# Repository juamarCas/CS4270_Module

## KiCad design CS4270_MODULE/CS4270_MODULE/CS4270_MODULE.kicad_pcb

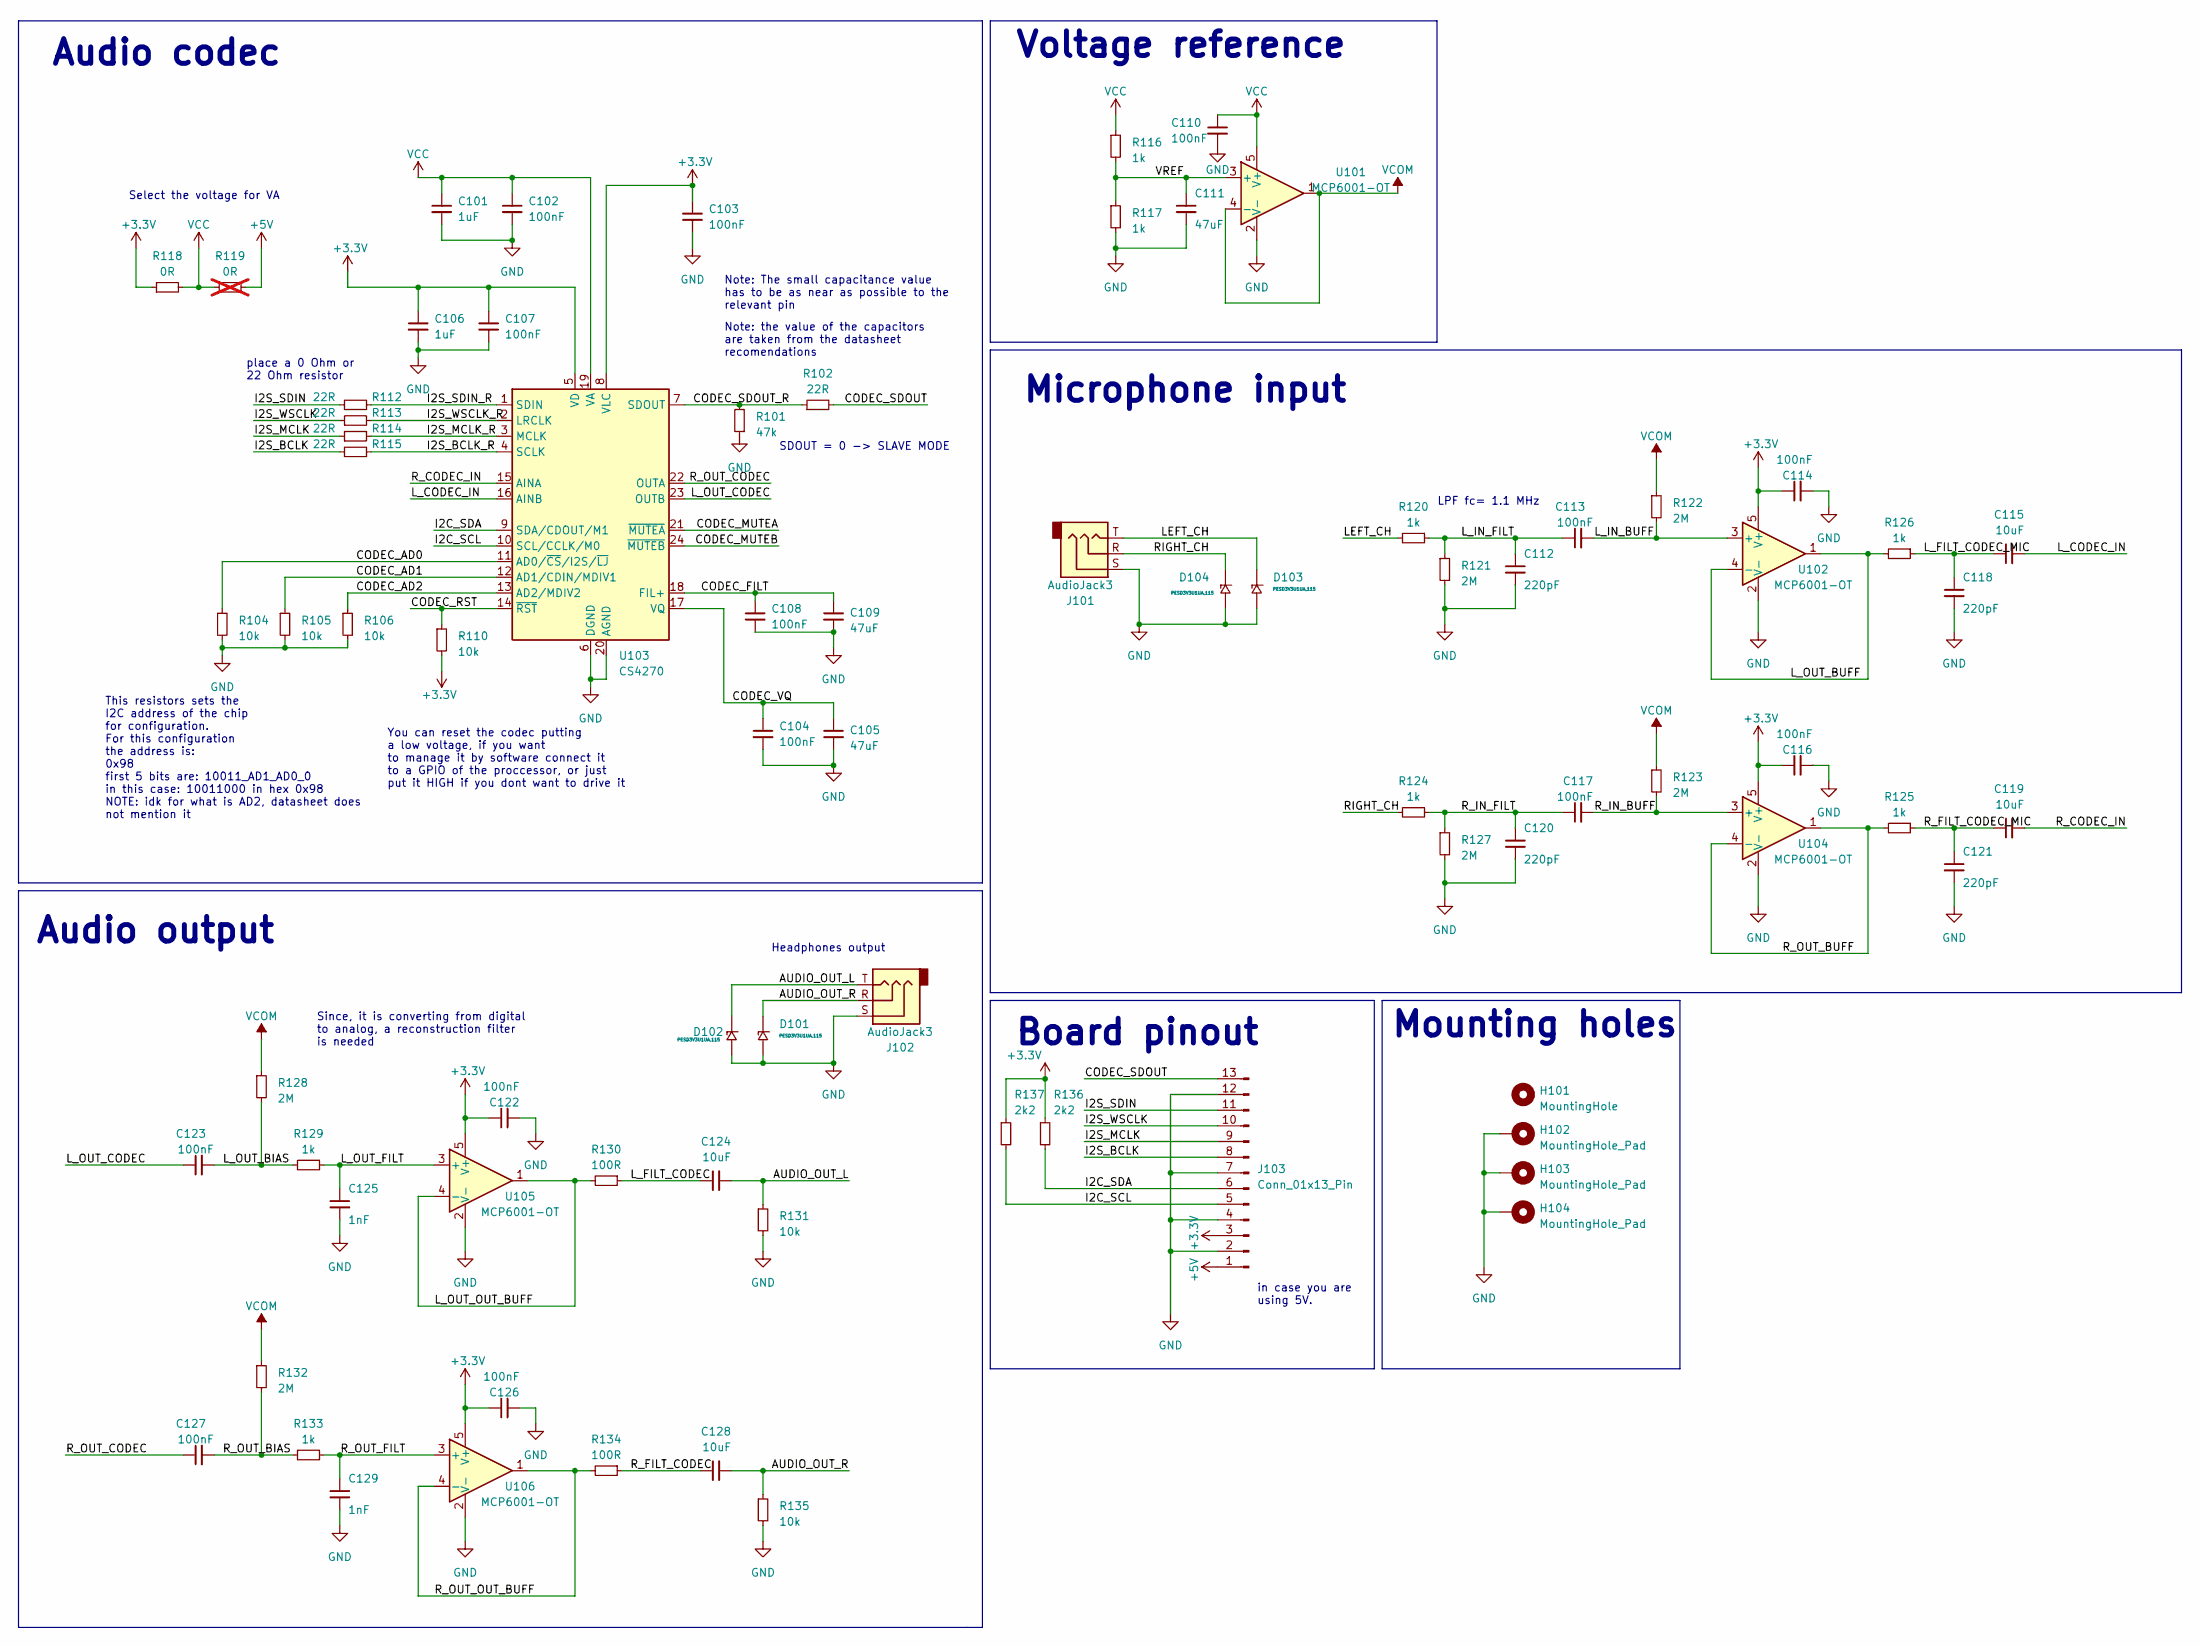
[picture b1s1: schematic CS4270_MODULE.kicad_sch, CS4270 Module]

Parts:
C101, C106: 1uF; C_0402_1005Metric; Mfr Part# GRM155R61E105MA12D
C102, C103, C104, C107, C108, C110, C113, C114, C116, C117, C122, C123, C126, C127: 100nF; C_0402_1005Metric; Mfr Part# C1005X7R1C104K050BC
C105, C109, C111: 47uF; C_0603_1608Metric; Mfr Part# 0603ZG474ZAT2A
C112, C118, C120, C121: 220pF; C_0603_1608Metric; Mfr Part# C0603C221G3HACTU
C115, C119, C124, C128: 10uF; C_0805_2012Metric; Mfr Part# GRM21BR61C106KE15K
C125, C129: 1nF; C_0402_1005Metric; Mfr Part# GRM1555C1H102JA1J
D101, D102, D103, D104: PESD3V3U1UA,115; SOD-323-2; Mfr Part# PESD3V3U1UA,115
H101: MountingHole; MountingHole_2.2mm_M2
H102: MountingHole_Pad; MountingHole_2.2mm_M2_Pad_TopBottom
H103, H104: MountingHole_Pad; MountingHole_2.2mm_M2_DIN965_Pad_TopBottom
J101, J102: AudioJack3; JAC_TRS_3.5mm_SMD; Mfr Part# 35RASMT2BHSNTRX
J103: Conn_01x13_Pin; PinHeader_1x13_P2.54mm_Vertical
R101: 47k; R_0603_1608Metric; Mfr Part# ERJ-3GEYJ473V
R102, R112, R113, R114, R115: 22R; R_0603_1608Metric; Mfr Part# ERJ-PA3F22R0V
R104, R105, R106, R110, R131, R135: 10k; R_0805_2012Metric; Mfr Part# CR0805-JW-103ELF
R116, R117, R120, R124, R125, R126, R129, R133: 1k; R_0603_1608Metric; Mfr Part# CR0603-FX-1001ELF
R118: 0R; R_0603_1608Metric; Mfr Part# ERJ-3GEY0R00V
R119: 0R; R_0603_1608Metric; Mfr Part# ERJ-3GEY0R00V; not fitted
R121, R122, R123, R127, R128, R132: 2M; R_0805_2012Metric; Mfr Part# RC0805JR-072M2L
R130, R134: 100R; R_0603_1608Metric; Mfr Part# CR0603-FX-1000ELF
R136, R137: 2k2; R_0805_2012Metric; Mfr Part# CR0805-JW-222ELF
U101, U102, U104, U105, U106: MCP6001-OT; SOT-23-5; Mfr Part# MCP6001UT-I/OT
U103: CS4270; TSSOP-24_4.4x7.8mm_P0.65mm; Mfr Part# CS4270-CZZ

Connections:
+3V3: C103.1, C106.1, C107.1, C114.1, C116.1, C122.1, C126.1, J103.3, R110.2, R118.1, R136.1, R137.1, U102.5 (V+), U103.5 (VD), U103.8 (VLC), U104.5 (V+), U105.5 (V+), U106.5 (V+)
+5V: J103.1, R119.2
/AUDIO_OUT_L: C124.2, D102.1 (K), J102.T, R131.1
/AUDIO_OUT_R: C128.2, D101.1 (K), J102.R, R135.1
/CODEC_AD0: R104.1, U103.11 (AD0/~CS/I2S/~LJ)
/CODEC_AD1: R105.1, U103.12 (AD1/CDIN/MDIV1)
/CODEC_AD2: R106.1, U103.13 (AD2/MDIV2)
/CODEC_FILT: C108.1, C109.1, U103.18 (FIL+)
/CODEC_MUTEA: U103.21 (~MUTEA)
/CODEC_MUTEB: U103.24 (~MUTEB)
/CODEC_RST: R110.1, U103.14 (~RST)
/CODEC_SDOUT: J103.13, R102.2
/CODEC_SDOUT_R: R101.2, R102.1, U103.7 (SDOUT)
/CODEC_VQ: C104.1, C105.1, U103.17 (VQ)
/I2C_SCL: J103.5, R137.2, U103.10 (SCL/CCLK/M0)
/I2C_SDA: J103.6, R136.2, U103.9 (SDA/CDOUT/M1)
/I2S_BCLK: J103.8, R115.1
/I2S_BCLK_R: R115.2, U103.4 (SCLK)
/I2S_MCLK: J103.9, R114.1
/I2S_MCLK_R: R114.2, U103.3 (MCLK)
/I2S_SDIN: J103.11, R112.1
/I2S_SDIN_R: R112.2, U103.1 (SDIN)
/I2S_WSCLK: J103.10, R113.1
/I2S_WSCLK_R: R113.2, U103.2 (LRCLK)
/LEFT_CH: D103.1 (K), J101.T, R120.2
/L_CODEC_IN: C115.2, U103.16 (AINB)
/L_FILT_CODEC: C124.1, R130.1
/L_FILT_CODEC_MIC: C115.1, C118.1, R126.1
/L_IN_BUFF: C113.2, R122.2, U102.3 (+)
/L_IN_FILT: C112.1, C113.1, R120.1, R121.1
/L_OUT_BIAS: C123.2, R128.2, R129.2
/L_OUT_BUFF: R126.2, U102.1, U102.4 (-)
/L_OUT_CODEC: C123.1, U103.23 (OUTB)
/L_OUT_FILT: C125.1, R129.1, U105.3 (+)
/L_OUT_OUT_BUFF: R130.2, U105.1, U105.4 (-)
/RIGHT_CH: D104.1 (K), J101.R, R124.2
/R_CODEC_IN: C119.2, U103.15 (AINA)
/R_FILT_CODEC: C128.1, R134.1
/R_FILT_CODEC_MIC: C119.1, C121.1, R125.1
/R_IN_BUFF: C117.2, R123.2, U104.3 (+)
/R_IN_FILT: C117.1, C120.1, R124.1, R127.1
/R_OUT_BIAS: C127.2, R132.2, R133.2
/R_OUT_BUFF: R125.2, U104.1, U104.4 (-)
/R_OUT_CODEC: C127.1, U103.22 (OUTA)
/R_OUT_FILT: C129.1, R133.1, U106.3 (+)
/R_OUT_OUT_BUFF: R134.2, U106.1, U106.4 (-)
/VREF: C111.1, R116.2, R117.1, U101.3 (+)
GND: C101.2, C102.2, C103.2, C104.2, C105.2, C106.2, C107.2, C108.2, C109.2, C110.2, C111.2, C112.2, C114.2, C116.2, C118.2, C120.2, C121.2, C122.2, C125.2, C126.2, C129.2, D101.2 (A), D102.2 (A), D103.2 (A), D104.2 (A), H102.1, H103.1, H104.1, J101.S, J102.S, J103.2, J103.4, J103.7, J103.12, R101.1, R104.2, R105.2, R106.2, R117.2, R121.2, R127.2, R131.2, R135.2, U101.2 (V-), U102.2 (V-), U103.6 (DGND), U103.20 (AGND), U104.2 (V-), U105.2 (V-), U106.2 (V-)
VCC: C101.1, C102.1, C110.1, R116.1, R118.2, R119.1, U101.5 (V+), U103.19 (VA)
VCOM: R122.1, R123.1, R128.1, R132.1, U101.1, U101.4 (-)

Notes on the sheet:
Audio output
SDOUT = 0 -> SLAVE MODE
You can reset the codec putting a low voltage, if you want to manage it by software connect it to a GPIO of the proccessor, or just put it HIGH if you dont want to drive it
LPF fc= 1.1 MHz
Headphones output
Since, it is converting from digital to analog, a reconstruction filter is needed
Note: The small capacitance value has to be as near as possible to the relevant pin
Voltage reference
place a 0 Ohm or 22 Ohm resistor
in case you are using 5V.
Mounting holes
Select the voltage for VA
Note: the value of the capacitors are taken from the datasheet recomendations
Board pinout
Audio codec
Microphone input
This resistors sets the I2C address of the chip for configuration. For this configuration the address is: 0x98 first 5 bits are: 10011_AD1_AD0_0 in this case: 10011000 in hex 0x98 NOTE: idk for what is AD2, datasheet does not mention it

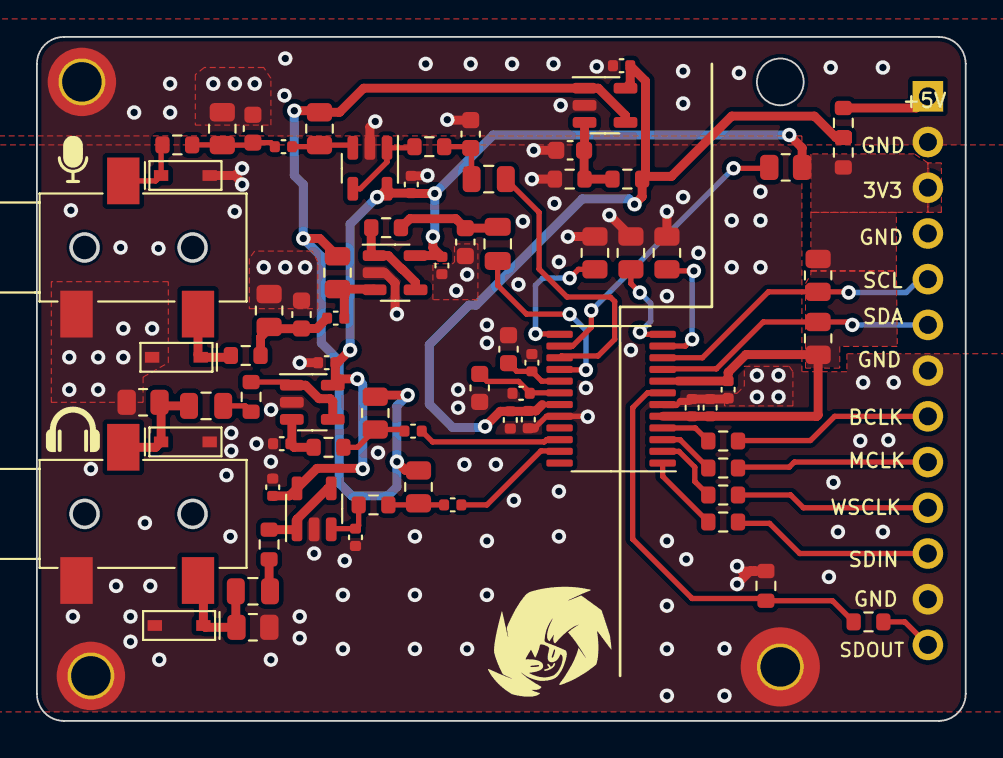
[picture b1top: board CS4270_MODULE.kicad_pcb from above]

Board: 4 copper layers, 51.6 x 38.0 mm, 77 parts (1 on the bottom side), 48 nets.

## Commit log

2023-02-22 finished PCB
